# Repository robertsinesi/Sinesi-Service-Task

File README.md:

# KLM SRAM Expansion — Service Task

Belle II KLM service work · Instrumentation Development Lab, University of Hawai'i at Mānoa

## Overview

The KLM scintillator readout currently shares a single SRAM between the Bus A and
Bus B firmware modules through the SCROD FPGA. During multi-strip hits, pedestal
fetching becomes the rate-limiting step in waveform processing. This project adds
a second SRAM on an auxiliary daughtercard so each bus has its own memory path,
along with the power-distribution hardware needed to supply it.

Three boards make up the system:

| Board | Function |
| --- | --- |
| **Aux SRAM daughtercard** | Mounts to the spare 80-pin mezzanine connector on the scintillator motherboard; carries the second SRAM and a local 3.3 V regulator |
| **RTM +5 V board** | Rear transition module; taps +5 V from the crate backplane, fuses it, and feeds the wiring harness |
| **2-pole fanout board** | Splits the 12 AWG trunk into 22 AWG drops, one per SRAM card |

**Board design credit:** all three boards were designed by Chris Ketter (UH Mānoa),
with contributions from Horacio Ledesma. My role is prototype testing and design
finalization.

## Scope of this qualification task

Testing and validation:

- Test the prototype SRAM expansion board on the UH KLM testbench
- Test the associated RTM and power-distribution boards
- Verify electrical connections and power delivery across the full chain
- Confirm correct operation with the dedicated SRAM firmware

Finalization:

- Feed prototype results back into the board designs
- Help finalize assembly procedures ahead of the production run

Superseded board revisions are kept in the `Old_Boards_Moved_<M-D-YY>/` folders (dated by when they were superseded, each with a short README); current files are in `Finalized-Boards/`.

## Deliverable

- Finalized board designs
- Production of the boards
- Installation of the boards

## After the qualification task

Continued contribution to board production, testing, and installation as part of
ongoing KLM service work.

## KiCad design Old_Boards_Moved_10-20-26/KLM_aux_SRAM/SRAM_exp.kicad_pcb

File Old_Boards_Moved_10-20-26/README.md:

Boards as of 10-20-26, archived before the hand-solderability revision.

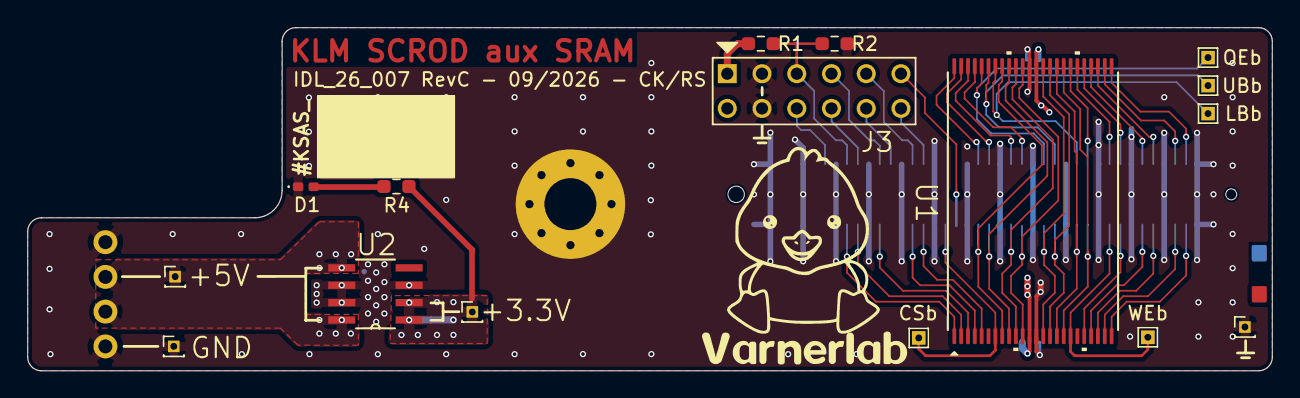
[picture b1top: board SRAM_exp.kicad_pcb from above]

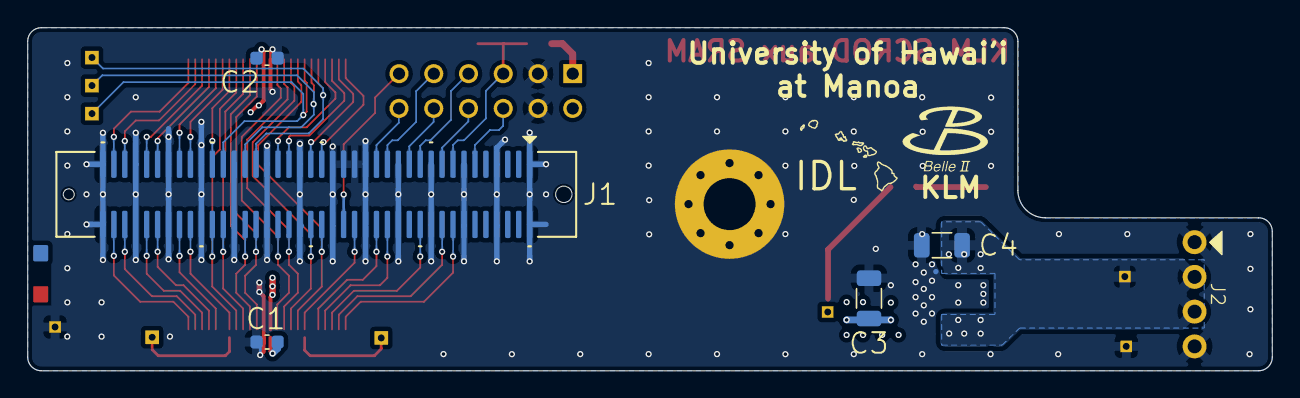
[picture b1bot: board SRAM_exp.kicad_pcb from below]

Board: 4 copper layers, 91.0 x 25.1 mm, 23 parts (6 on the bottom side), 46 nets.

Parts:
C1, C2: 10u; C_0603_1608Metric
C3, C4: 100u; C_1206_3216Metric
D1: LED; LED_0402_1005Metric_Pad0.77x0.64mm_HandSolder
H2: MountingHole_Pad_Via_6-32_free_fit
J1: conn_80pin; CONN_5177985-3_TYC
J2: Conn_01x04; Molex_01x04_RA_22-05-3041
J3: Pmod_conn; CONN_HEADER_VERT_12POS_2.54MM
R1: 330; R_0603_1608Metric_Pad0.98x0.95mm_HandSolder
R2: 1k; R_0603_1608Metric_Pad0.98x0.95mm_HandSolder
R4: 1.3k; R_0603_1608Metric_Pad0.98x0.95mm_HandSolder
TP1: +5V; PinHeader_1x01_P1.00mm_Vertical
TP2: +3.3V; PinHeader_1x01_P1.00mm_Vertical
TP3, TP11: GND; PinHeader_1x01_P1.00mm_Vertical
TP4: OEb; TestPoint_THTPad_1.0x1.0mm_Drill0.5mm
TP5: UBb; TestPoint_THTPad_1.0x1.0mm_Drill0.5mm
TP6: LBb; TestPoint_THTPad_1.0x1.0mm_Drill0.5mm
TP7: WEb; TestPoint_THTPad_1.0x1.0mm_Drill0.5mm
TP8: CSb; TestPoint_THTPad_1.0x1.0mm_Drill0.5mm
U1: IS61WV204816BLL-10TLI; 48L_TSOP-1_12X20_ISI
U2: LT1963AES8-3.3PBF; SOIC127P600X175-8N

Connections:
+3.3V: C1.2, C2.2, C3.1, J3.1, J3.7, R1.1, R4.1, TP2.1 (1_1), U1.12 (VDD), U1.36 (VDD), U2.1 (OUT), U2.2 (SENSE)
+5V: C4.1, J2.2, J2.3, TP1.1 (1_1), U2.5 (~SHDN), U2.8 (IN)
/A0: J1.66, U1.5 (A0)
/A1: J1.67, U1.4 (A1)
/A2: J1.70, U1.3 (A2)
/A3: J1.72, U1.2 (A3)
/A4: J1.73, U1.1 (A4)
/A5: J1.20, U1.48 (A5)
/A6: J1.21, U1.47 (A6)
/A7: J1.23, U1.46 (A7)
/A8: J1.24, U1.45 (A8)
/A9: J1.32, U1.30 (A9)
/A10: J1.33, U1.29 (A10)
/A11: J1.35, U1.28 (A11)
/A12: J1.36, U1.27 (A12)
/A13: J1.38, U1.26 (A13)
/A14: J1.39, U1.25 (A14)
/A15: J1.42, U1.24 (A15)
/A16: J1.43, U1.23 (A16)
/A17: J1.45, U1.22 (A17)
/A18: J1.46, U1.21 (A18)
/A19: J1.48, U1.20 (A19)
/A20: J1.30, U1.31 (A20)
/IO0: J1.61, U1.8 (I/O0), U1.41 (I/O15)
/IO1: J1.60, U1.9 (I/O1), U1.40 (I/O14)
/IO2: J1.58, U1.10 (I/O2), U1.39 (I/O13)
/IO3: J1.57, U1.11 (I/O3), U1.38 (I/O12)
/IO4: J1.55, U1.14 (I/O4), U1.35 (I/O11)
/IO5: J1.54, U1.15 (I/O5), U1.34 (I/O10)
/IO6: J1.52, U1.16 (I/O6), U1.33 (I/O9)
/IO7: J1.51, U1.17 (I/O7), U1.32 (I/O8)
/spare0: J1.6, J3.9
/spare1: J1.8, J3.3, R1.2, R2.1
/spare2: J1.9, J3.10
/spare3: J1.11, J3.4
/spare4: J1.12, J3.11
/spare5: J1.14, J3.5
/spare6: J1.15, J3.12
/spare7: J1.63, J3.6
GND: C1.1, C2.1, C3.2, C4.2, D1.1 (K), H2.1 (1_1), J1.1, J1.4, J1.7, J1.10, J1.13, J1.16, J1.17, J1.18, J1.19, J1.22, J1.25, J1.28, J1.31, J1.34, J1.37, J1.40, J1.41, J1.44, J1.47, J1.50, J1.53, J1.56, J1.59, J1.62, J1.65, J1.68, J1.71, J1.74, J1.77, J1.80, J2.1, J2.4, J3.2, J3.8, R2.2, TP3.1 (1_1), TP11.1 (1_1), U1.13 (VSS), U1.37 (VSS), U2.3 (GND_3), U2.6 (GND_2), U2.7 (GND)
unnamed: D1.2 (A), R4.2
unnamed: J1.64, TP8.1 (1_1), U1.7 (CS#)
unnamed: J1.29, TP6.1 (1_1), U1.42 (LB#)
unnamed: J1.26, TP4.1 (1_1), U1.44 (OE#)
unnamed: J1.27, TP5.1 (1_1), U1.43 (UB#)
unnamed: J1.49, TP7.1 (1_1), U1.18 (WE#)

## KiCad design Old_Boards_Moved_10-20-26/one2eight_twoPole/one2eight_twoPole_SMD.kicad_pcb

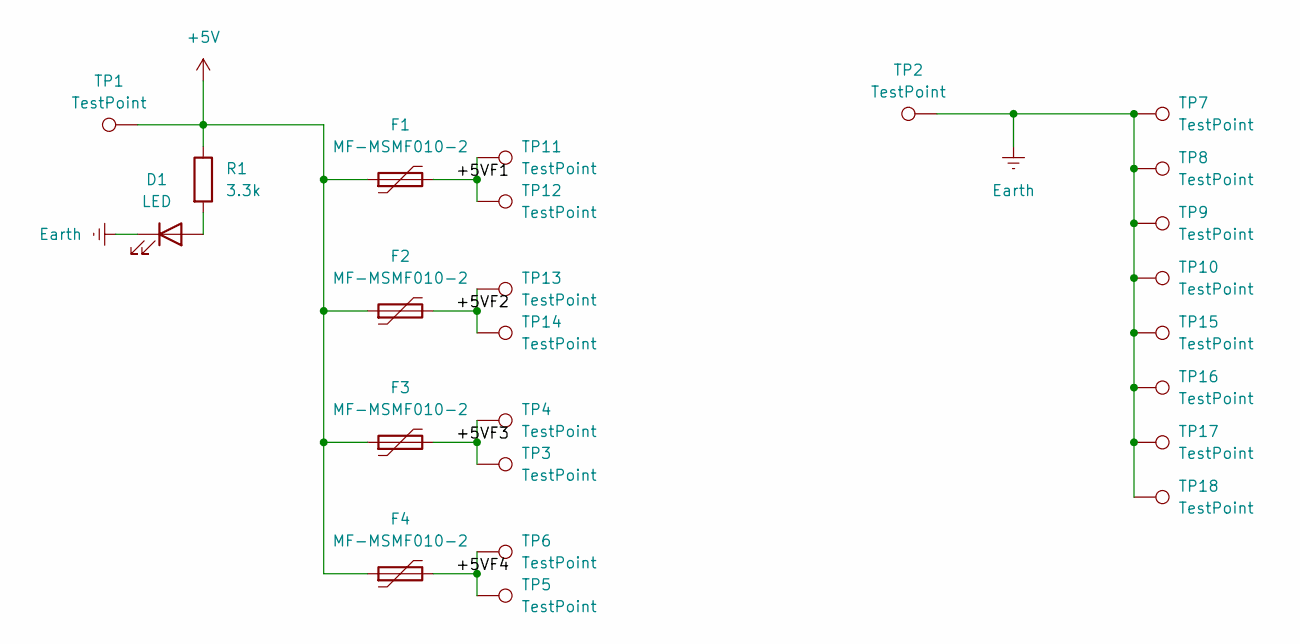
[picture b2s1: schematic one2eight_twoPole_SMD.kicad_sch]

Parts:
D1: LED; LED_0402_1005Metric_Pad0.77x0.64mm_HandSolder
F1, F2, F3, F4: MF-MSMF010-2; Fuse_1812_4532Metric
R1: 3.3k; R_0603_1608Metric_Pad0.98x0.95mm_HandSolder
TP1, TP2: TestPoint; PTH_12AWG
TP3, TP4, TP5, TP6, TP7, TP8, TP9, TP10, TP11, TP12, TP13, TP14, TP15, TP16, TP17, TP18: TestPoint; SolderWire-0.5sqmm_1x01_D0.9mm_OD2.1mm_Relief_3mm_shorter_v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

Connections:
+5V: F1.1, F2.1, F3.1, F4.1, R1.1, TP1.1 (1_1)
/+5VF1: F1.2, TP11.1 (1_1), TP12.1 (1_1)
/+5VF2: F2.2, TP13.1 (1_1), TP14.1 (1_1)
/+5VF3: F3.2, TP3.1 (1_1), TP4.1 (1_1)
/+5VF4: F4.2, TP5.1 (1_1), TP6.1 (1_1)
Earth: D1.1 (K), TP2.1 (1_1), TP7.1 (1_1), TP8.1 (1_1), TP9.1 (1_1), TP10.1 (1_1), TP15.1 (1_1), TP16.1 (1_1), TP17.1 (1_1), TP18.1 (1_1)
unnamed: D1.2 (A), R1.2

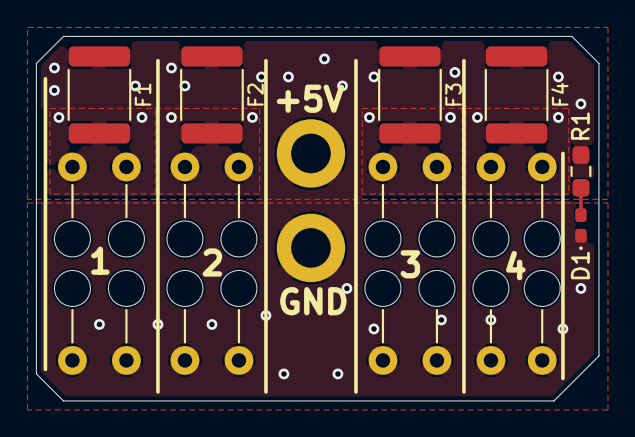
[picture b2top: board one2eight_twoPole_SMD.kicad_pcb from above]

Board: 4 copper layers, 31.2 x 20.2 mm, 24 parts (0 on the bottom side), 7 nets.

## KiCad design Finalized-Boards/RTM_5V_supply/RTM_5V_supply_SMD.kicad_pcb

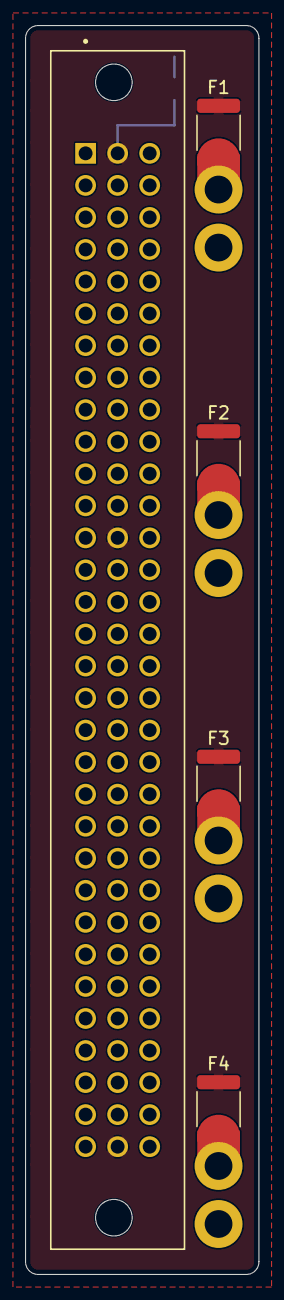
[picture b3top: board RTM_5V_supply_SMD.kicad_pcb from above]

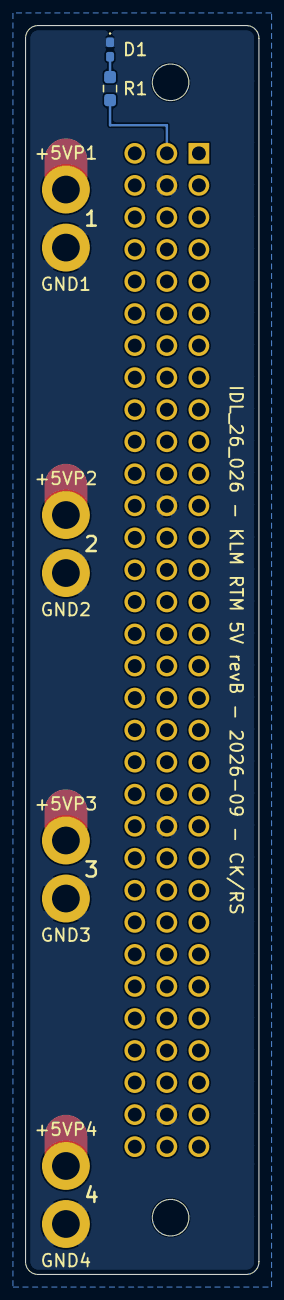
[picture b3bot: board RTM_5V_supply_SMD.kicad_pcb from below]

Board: 4 copper layers, 18.5 x 99.0 mm, 15 parts (10 on the bottom side), 7 nets.

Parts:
+5VP1, +5VP2, +5VP3, +5VP4: SolderWire_PTH; PTH_12AWG
D1: LED; LED_0402_1005Metric_Pad0.77x0.64mm_HandSolder
F1, F2, F3, F4: MF-MSMF030-2; Fuse_1812_4532Metric
GND1, GND2, GND3, GND4: SolderWire_PTH; PTH_12AWG
J1: 86093968114755V1LF; AMPHENOL_86093968114755V1LF
R1: 3.3k; R_0603_1608Metric_Pad0.98x0.95mm_HandSolder

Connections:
+5V: F1.1, F2.1, F3.1, F4.1, J1.B1, J1.B13, J1.B32, R1.1
GND: D1.1 (K), GND1.1 (1_1), GND2.1 (1_1), GND3.1 (1_1), GND4.1 (1_1), J1.B2, J1.B12, J1.B22, J1.B31
unnamed: +5VP1.1 (1_1), F1.2
unnamed: +5VP2.1 (1_1), F2.2
unnamed: +5VP3.1 (1_1), F3.2
unnamed: +5VP4.1 (1_1), F4.2
unnamed: D1.2 (A), R1.2

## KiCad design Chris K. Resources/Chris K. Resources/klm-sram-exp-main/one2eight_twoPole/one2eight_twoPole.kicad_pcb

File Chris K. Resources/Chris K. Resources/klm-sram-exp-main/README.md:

# KLM SRAM Exp

## KLM SRAM Upgrade project
We are using a spare 80-pin connector on the motherboard to double the amount and bandwidth of SRAM available to our FPGA.

## Firmware
The new firmware for this project has been created in the main SCROD FW repository under the branch feature/SRAM_upgrade.

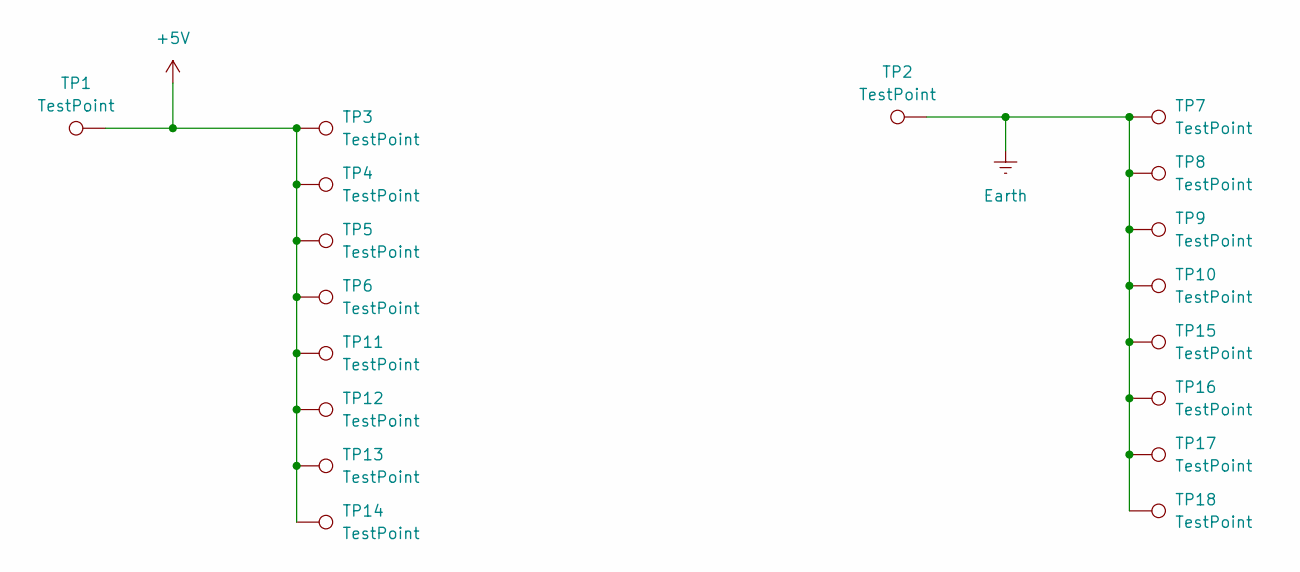
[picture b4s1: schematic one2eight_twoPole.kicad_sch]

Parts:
TP1, TP2: TestPoint; SolderWire-4sqmm_1x01_D3mm_OD6mm_Relief
TP3, TP4, TP5, TP6, TP7, TP8, TP9, TP10, TP11, TP12, TP13, TP14, TP15, TP16, TP17, TP18: TestPoint; SolderWire-0.5sqmm_1x01_D0.9mm_OD2.1mm_Relief

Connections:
+5V: TP1.1, TP3.1, TP4.1, TP5.1, TP6.1, TP11.1, TP12.1, TP13.1, TP14.1
Earth: TP2.1, TP7.1, TP8.1, TP9.1, TP10.1, TP15.1, TP16.1, TP17.1, TP18.1

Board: 4 copper layers, 18 parts (0 on the bottom side), 2 nets, no tracks yet.
